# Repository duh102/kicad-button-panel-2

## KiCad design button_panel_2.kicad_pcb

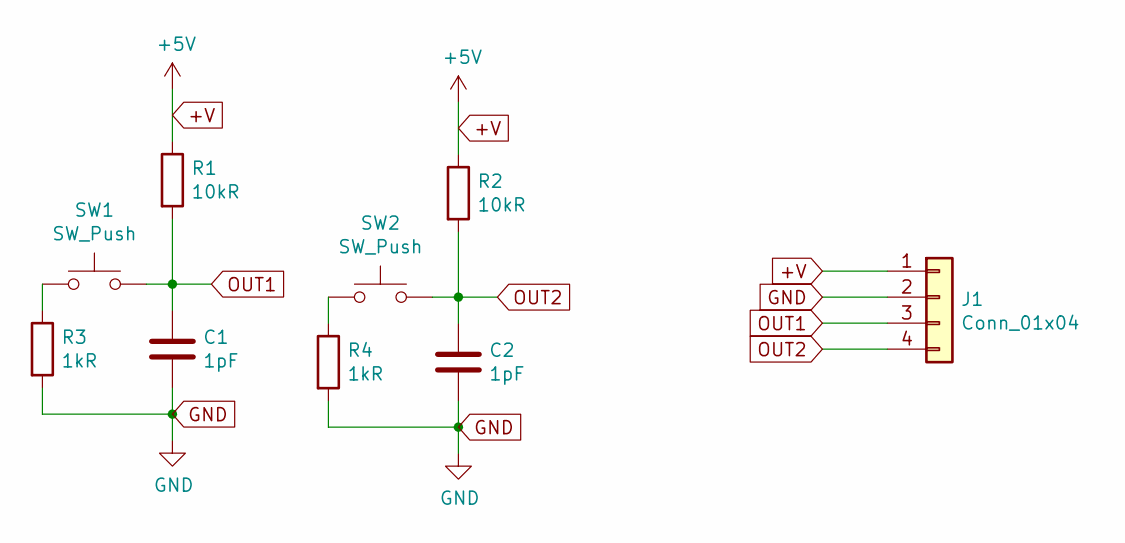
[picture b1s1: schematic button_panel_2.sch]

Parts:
C1, C2: 1pF; C_0805_2012Metric
J1: Conn_01x04; PinHeader_1x04_P2.54mm_Vertical
R1, R2: 10kR; R_0805_2012Metric
R3, R4: 1kR; R_0805_2012Metric
SW1, SW2: SW_Push; SW_Push_1P1T_NO_CK_KMR2

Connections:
+V: J1.1, R1.1, R2.1
GND: C1.2, C2.2, J1.2, R3.2, R4.2
unnamed: R3.1, SW1.1
unnamed: R4.1, SW2.1
OUT1: C1.1, J1.3, R1.2, SW1.2
OUT2: C2.1, J1.4, R2.2, SW2.2

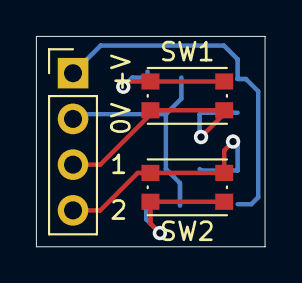
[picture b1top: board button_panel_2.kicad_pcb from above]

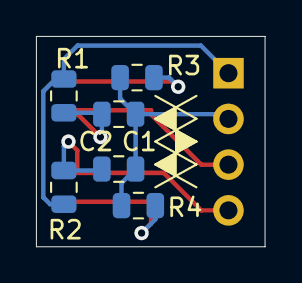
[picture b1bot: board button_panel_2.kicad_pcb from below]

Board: 2 copper layers, 12.7 x 11.7 mm, 9 parts (6 on the bottom side), 6 nets.
